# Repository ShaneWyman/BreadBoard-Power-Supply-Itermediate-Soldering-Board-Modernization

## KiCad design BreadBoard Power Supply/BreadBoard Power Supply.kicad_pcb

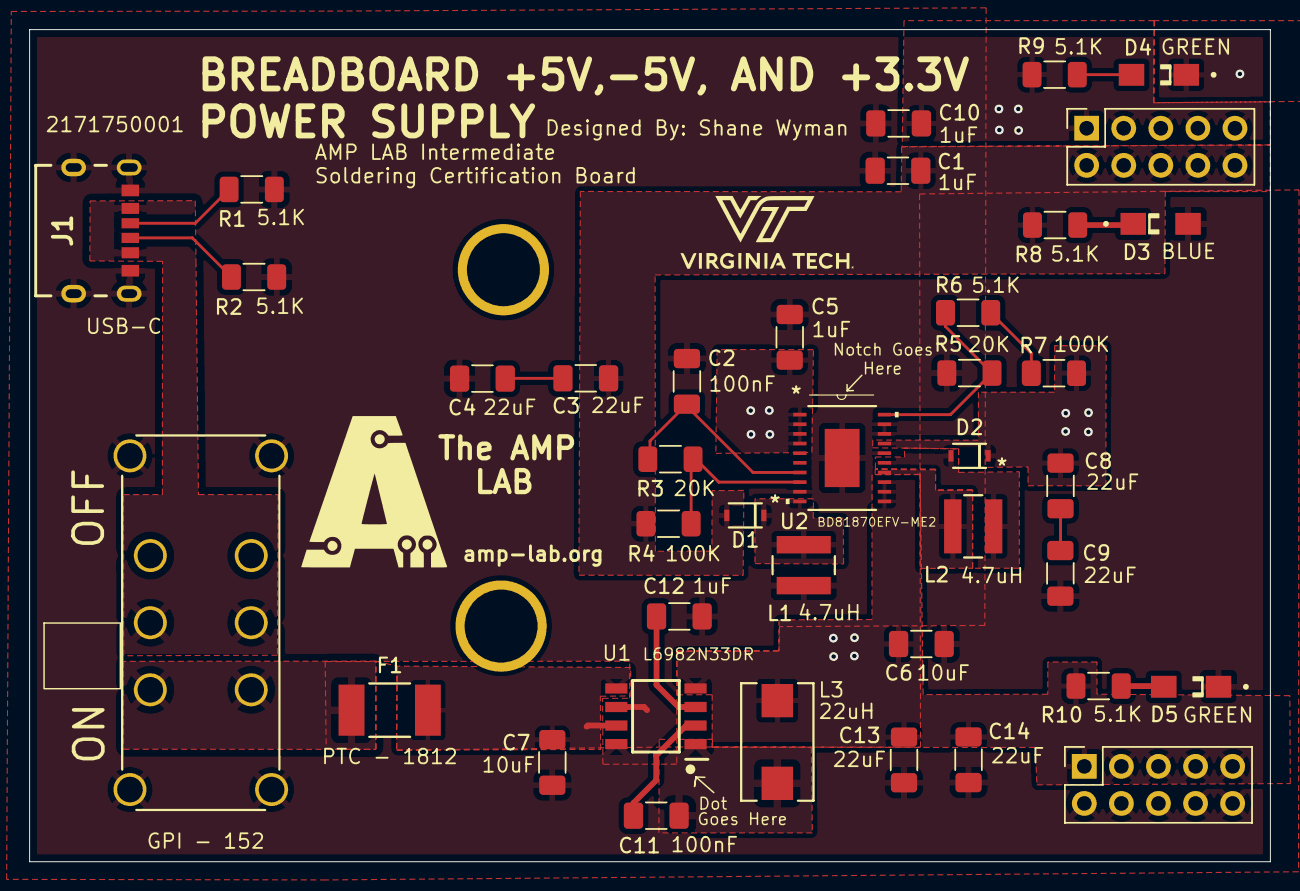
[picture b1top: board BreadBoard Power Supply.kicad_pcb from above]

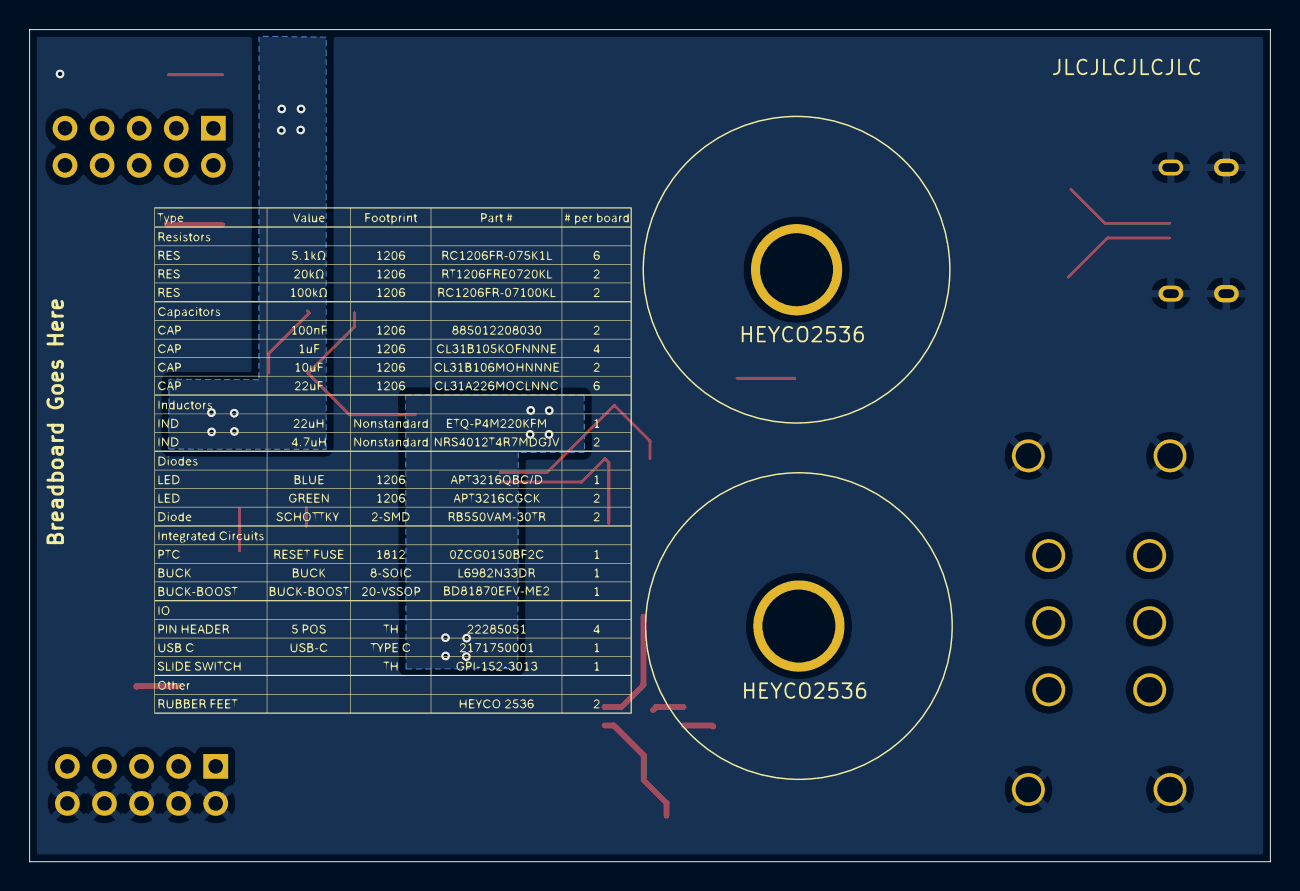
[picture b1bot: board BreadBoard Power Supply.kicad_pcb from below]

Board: 2 copper layers, 85.0 x 57.0 mm, 41 parts (2 on the bottom side), 24 nets.

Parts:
C1, C5, C10, C12: 1uF; C_1206_3216Metric_Pad1.33x1.80mm_HandSolder
C2, C11: 100nF; C_1206_3216Metric_Pad1.33x1.80mm_HandSolder
C3, C4, C8, C9, C13, C14: 22uF; C_1206_3216Metric_Pad1.33x1.80mm_HandSolder
C6, C7: 10uF; C_1206_3216Metric_Pad1.33x1.80mm_HandSolder
D1, D2: RB550VAM-30TR; DIO_RB160VAM_ROM-L
D3: APT3216QBC/D; LED_APT3216QBC_D
D4, D5: APT3216CGCK; LED_APT3216QBC_D
F1: 0ZCG0150BF2C; 0ZCG_BEL
H1, H2: MountingHole; RubberFoot
J1: 2171750001
J2, J3: Conn_02x05_Top_Bottom; PinSocket_2x05_P2.54mm_Vertical
L1, L2: 4.7uH; IND_NRS4012T100MDGJV_TAY
L3: 22uH; IND_PCC-M0748M-LE_PAN-L
R1, R2, R6, R8, R9, R10: 5.1k; R_1206_3216Metric_Pad1.30x1.75mm_HandSolder
R3, R5: 20k; R_1206_3216Metric_Pad1.30x1.75mm_HandSolder
R4, R7: 100k; R_1206_3216Metric_Pad1.30x1.75mm_HandSolder
U1: GPI-152-3013; SW_GPI-152-3013_CWI
U1#2: L6982N33DR; SOIC127P600X175-8N
U2: BD81870EFV-ME2; HTSSOP-B20_ROM-L

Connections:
+3.3V: C5.2, C6.2, C13.2, C14.2, J3.1, J3.3, J3.5, J3.7, J3.9, L3.2, R10.2, U1#2.4 (VOUT/FB), U2.1 (VDDA), U2.2 (STB2), U2.3 (STB1), U2.4 (SEQON), U2.11 (VDDP), U2.12 (VDDP), U2.13 (VDDP)
+5V: C8.1, C10.2, D2.1 (K), J2.1, J2.3, J2.5, J2.7, J2.9, R7.2, R9.2, U2.17 (VOUT2)
-5V: C1.2, C3.1, D1.2 (A), J2.2, J2.4, J2.6, J2.8, J2.10, R4.2, R8.2
GND: C1.1, C2.2, C4.2, C5.1, C6.1, C7.1, C9.2, C10.1, C12.2, C13.1, C14.1, D3.2 (A), D4.1 (K), D5.1 (K), J1.A12 (GND_2), J1.B12 (GND), J1.MH1, J1.MH2, J1.MH3, J1.MH4, J3.2, J3.4, J3.6, J3.8, J3.10, L1.1, R1.1, R2.2, R5.1, U1.7, U1.8, U1.9, U1.10, U1#2.6 (AGND), U1#2.8 (PGND), U2.9 (DIS1), U2.16 (GNDP), U2.18 (DIS2), U2.19 (GNDA), U2.EPAD
unnamed: C3.2, C4.1
unnamed: C8.2, C9.1
unnamed: D1.1 (K), L1.2, U2.10 (LX1)
unnamed: D2.2 (A), L2.2, U2.15 (LX2)
unnamed: D3.1 (K), R8.1
unnamed: D4.2 (A), R9.1
unnamed: D5.2 (A), R10.1
unnamed: C11.2, U1#2.2 (BOOT)
unnamed: C7.2, F1.2, U1#2.5 (EN/CLKIN(~)), U1#2.7 (VIN)
unnamed: C11.1, L3.1, U1#2.1 (SW)
unnamed: C12.1, U1#2.3 (VCC)
unnamed: J1.A5 (CC1), R1.2
unnamed: J1.B5 (CC2), R2.1
unnamed: R6.2, R7.1
unnamed: L2.1, U2.14 (HS2L)
unnamed: R5.2, R6.1, U2.20 (INV2)
unnamed: R3.2, R4.1, U2.8 (NON1)
unnamed: C2.1, R3.1, U2.7 (VREF)
SWITCHED_VOLTAGE: F1.1, U1.3, U1.4
USB_VOLTAGE: J1.A9 (VBUS_2), J1.B9 (VBUS), U1.2, U1.5

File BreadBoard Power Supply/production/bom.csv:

Designator,Footprint,Quantity,Value,LCSC Part #
"C1, C10, C12, C5",1206,4,1uF,
"C11, C2",1206,2,100nF,
"C13, C14, C3, C4, C8, C9",1206,6,22uF,
"C6, C7",1206,2,10uF,
"D1, D2",DIO_RB160VAM_ROM-L,2,RB550VAM-30TR,
D3,LED_APT3216QBC_D,1,APT3216QBC/D,
"D4, D5",LED_APT3216QBC_D,2,APT3216CGCK,
F1,0ZCG_BEL,1,0ZCG0150BF2C,
J1,2171750001,1,2171750001,
"J2, J3",PinSocket_2x05_P2.54mm_Vertical,2,Conn_02x05_Top_Bottom,
"L1, L2",IND_NRS4012T100MDGJV_TAY,2,4.7uH,
L3,IND_PCC-M0748M-LE_PAN-L,1,22uH,
"R1, R10, R2, R6, R8, R9",1206,6,5.1k,
"R3, R5",1206,2,20k,
"R4, R7",1206,2,100k,
U1_2,SW_GPI-152-3013_CWI,1,GPI-152-3013,
U1,SOIC127P600X175-8N,1,L6982N33DR,
U2,HTSSOP-B20_ROM-L,1,BD81870EFV-ME2,

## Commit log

2025-10-01 Project Start
2025-10-04 Schematic work
2025-10-06 PCB work
2025-10-09 Pushing Proto 1 Files
